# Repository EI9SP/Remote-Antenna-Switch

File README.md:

# Remote Antenna Switch
Four to one Remote Antenna Switch, Full duplex RS485.
Project contains:
4 to 1 remote switch with Atmel ATmega_328 chip on board.
Controller with ESP32 OLED display.
Communication betwen the modules is done over CAT5/CAT6 Cable utilising full duplex RS485 and 13.8V Power.

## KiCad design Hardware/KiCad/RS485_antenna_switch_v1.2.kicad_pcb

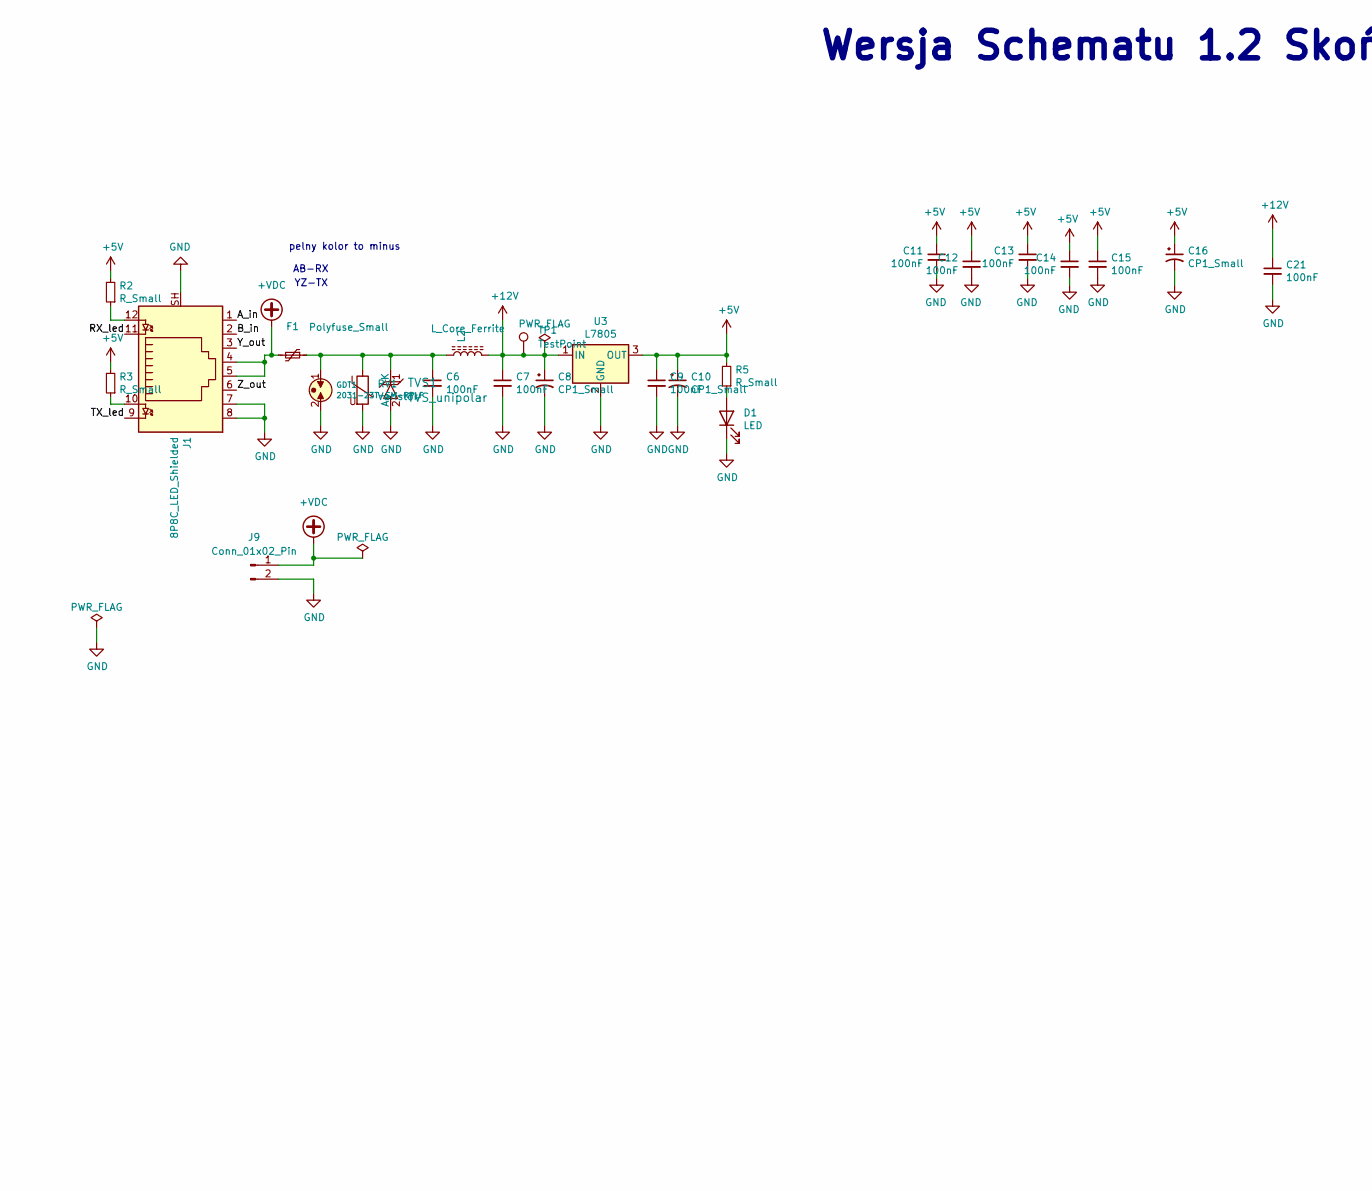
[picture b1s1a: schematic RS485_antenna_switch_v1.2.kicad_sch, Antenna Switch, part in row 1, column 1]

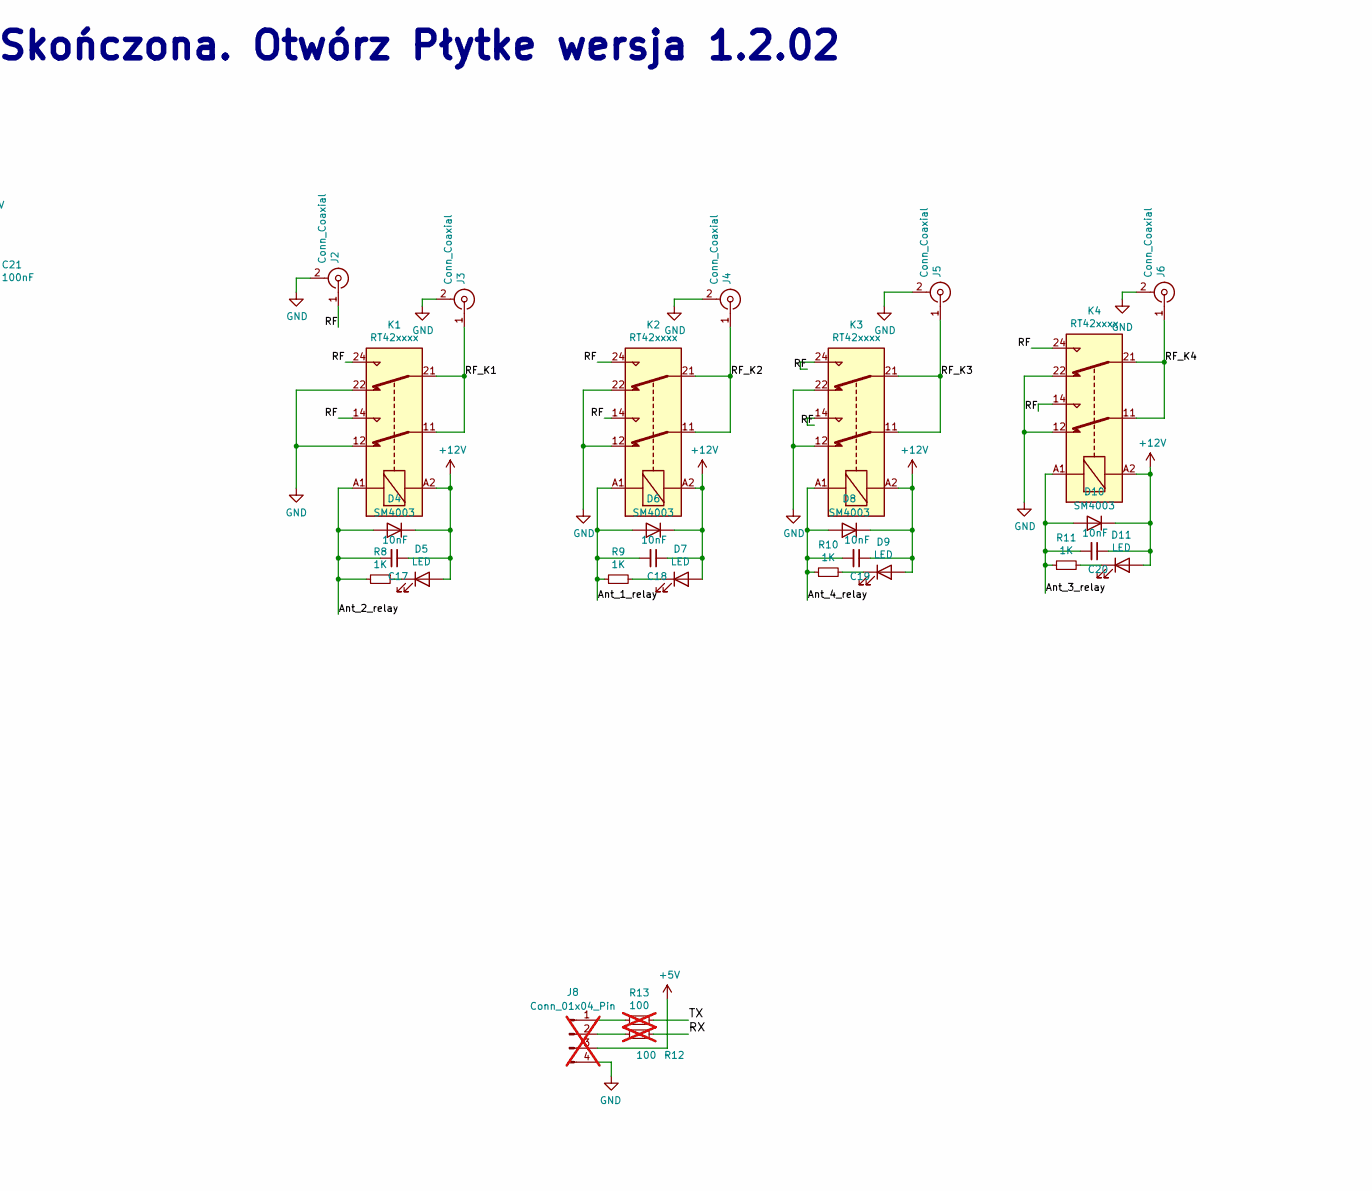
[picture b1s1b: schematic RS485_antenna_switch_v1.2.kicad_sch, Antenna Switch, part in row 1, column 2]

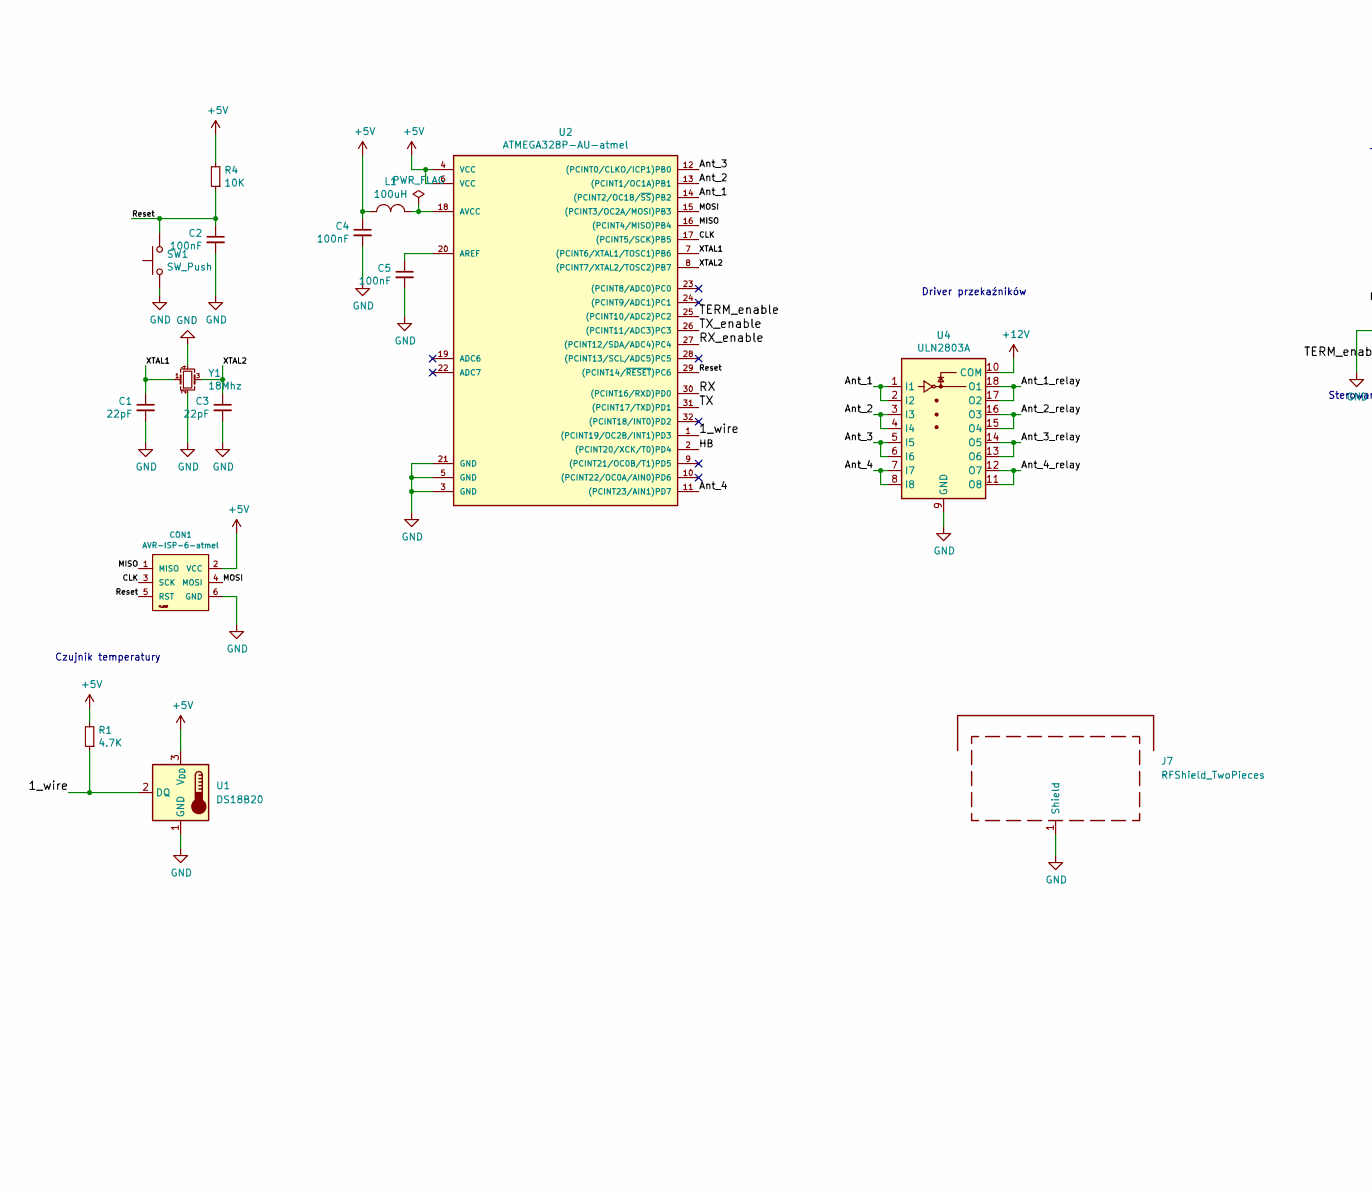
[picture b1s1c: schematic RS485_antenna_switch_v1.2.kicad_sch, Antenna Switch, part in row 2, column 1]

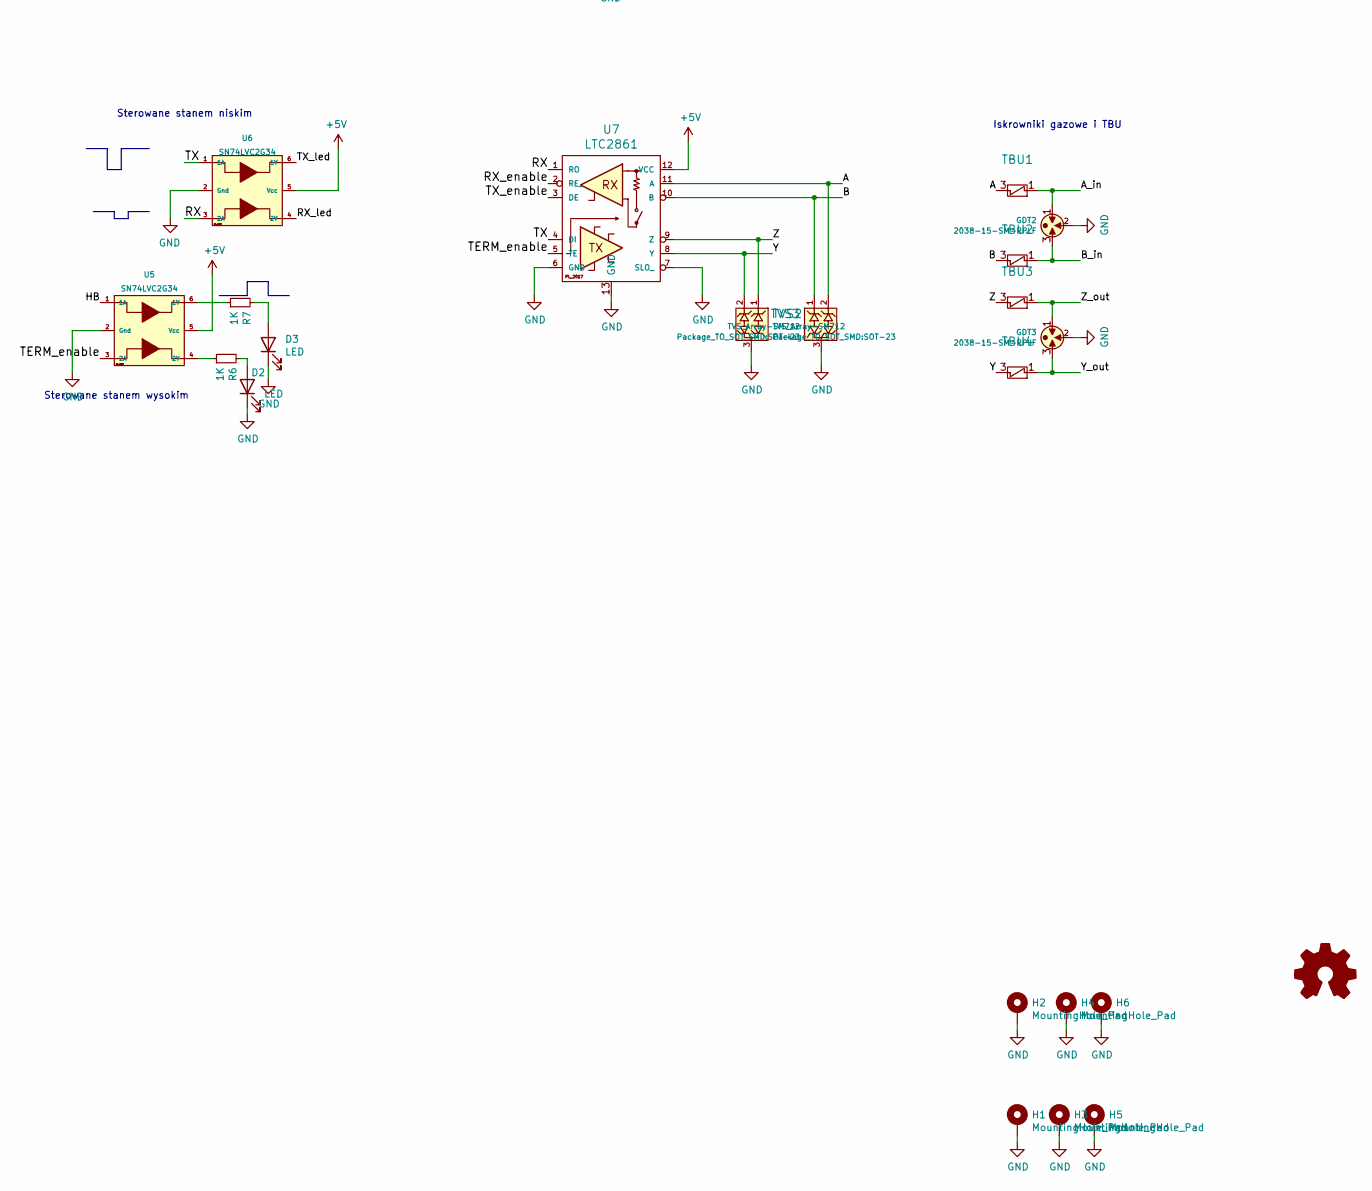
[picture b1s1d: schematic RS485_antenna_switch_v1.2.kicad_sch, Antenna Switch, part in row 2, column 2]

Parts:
C1: 22pF; C_0603_1608Metric
C2, C4, C5, C6, C7, C9, C11, C12, C13, C14, C15, C21: 100nF; C_0805_2012Metric
C3: 22pF; R_0603_1608Metric
C8, C10: CP1_Small; CP_EIA-7343-31_Kemet-D
C16: CP1_Small; CP_Elec_5x5.9
C17, C18, C19, C20: 10nF; C_0805_2012Metric
CON1: AVR-ISP-6-atmel; IDC-Header_2x03_P2.54mm_Vertical
D1, D2, D3: LED; LED_0805_2012Metric
D4, D6, D8, D10: SM4003; D_MELF
D5, D7, D9, D11: LED; LED_D3.0mm
F1: Polyfuse_Small; Fuse_Bourns_MF-SM_7.98x5.44mm
GDT1: 2031-23T-SM-RPLF; GDT-2027-XX-SM
GDT2, GDT3: 2038-15-SM-RPLF; GDT_2038-xx-SM
H1, H2, H3, H4, H5, H6: MountingHole_Pad; MountingHole_3.2mm_M3_Pad_Via
J1: 8P8C_LED_Shielded; RJ45_BEL_SS74301-00x_Vertical
J2, J3, J4, J5, J6: Conn_Coaxial; SO-239
J7: RFShield_TwoPieces
J8: Conn_01x04_Pin; Molex_KK-254_AE-6410-04A_1x04_P2.54mm_Vertical; not fitted
J9: Conn_01x02_Pin; PhoenixContact_MSTBVA_2,5_2-G-5,08_1x02_P5.08mm_Vertical
K1, K2, K3, K4: RT42xxxx; Relay_DPDT_Schrack-RT2-FormC_RM5mm
L1: 100uH; L_1812_4532Metric
L2: L_Core_Ferrite; Custom_inductors-BL01RN1A
R1: 4.7K; R_0805_2012Metric
R2, R3, R5: R_Small; R_0805_2012Metric
R4: 10K; R_0805_2012Metric
R6, R7, R8, R9, R10, R11: 1K; R_0805_2012Metric
R12, R13: 100; R_0805_2012Metric; not fitted
RV1: Varistor; RV_Disc_D12mm_W4.2mm_P7.5mm
SW1: SW_Push; SW_TH_Tactile_Omron_B3F-10xx
TBU1, TBU2, TBU3, TBU4: TBU_HSP; TBU-CA
TP1: TestPoint; TestPoint_THTPad_D2.0mm_Drill1.0mm
TVS1: TVS_unipolar; D_SMA
TVS2, TVS3: TVS_Array-SM712; SOT-23
U1: DS18B20; TO-92_HandSolder
U2: ATMEGA328P-AU-atmel; TQFP-32_7x7mm_P0.8mm
U3: L7805; d2-pak_termal
U4: ULN2803A; SOIC-18W_7.5x11.6mm_P1.27mm
U5, U6: SN74LVC2G34; SOT-23-6
U7: LTC2861; DFN-12-1EP_3x4mm_P0.5mm_EP1.7x3.3mm
Y1: 18Mhz; Crystal_SMD_5032-4Pin_5.0x3.2mm

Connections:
+5V: C4.1, C9.1, C10.1, C11.1, C12.1, C13.1, C14.1, C15.1, C16.1, CON1.2 (VCC), J8.3, L1.1, R1.2, R2.2, R3.2, R4.2, R5.2, U1.3 (V_{DD}), U2.4 (VCC), U2.6 (VCC), U3.3 (OUT), U5.5 (Vcc), U6.5 (Vcc), U7.12 (VCC)
+12V: C7.1, C8.1, C17.1, C18.1, C19.1, C20.1, C21.1, D4.1 (K), D5.2 (A), D6.1 (K), D7.2 (A), D8.1 (K), D9.2 (A), D10.1 (K), D11.2 (A), K1.A2, K2.A2, K3.A2, K4.A2, L2.2, TP1.1, U3.1 (IN), U4.10 (COM)
+VDC: F1.2, J1.4, J1.5, J9.1
/1_wire: R1.1, U1.2 (DQ), U2.1 ((PCINT19/OC2B/INT1)PD3)
/A: TBU1.3, TVS3.2, U7.11 (A)
/A_in: GDT2.1, J1.1, TBU1.1
/Ant_1: U2.14 ((PCINT2/OC1B/~SS)PB2), U4.1 (I1), U4.2 (I2)
/Ant_1_relay: C18.2, D6.2 (A), K2.A1, R9.1, U4.17 (O2), U4.18 (O1)
/Ant_2: U2.13 ((PCINT1/OC1A)PB1), U4.3 (I3), U4.4 (I4)
/Ant_2_relay: C17.2, D4.2 (A), K1.A1, R8.2, U4.15 (O4), U4.16 (O3)
/Ant_3: U2.12 ((PCINT0/CLKO/ICP1)PB0), U4.5 (I5), U4.6 (I6)
/Ant_3_relay: C20.2, D10.2 (A), K4.A1, R11.1, U4.13 (O6), U4.14 (O5)
/Ant_4: U2.11 ((PCINT23/AIN1)PD7), U4.7 (I7), U4.8 (I8)
/Ant_4_relay: C19.2, D8.2 (A), K3.A1, R10.1, U4.11 (O8), U4.12 (O7)
/B: TBU2.3, TVS3.1, U7.10 (B)
/B_in: GDT2.3, J1.2, TBU2.1
/CLK: CON1.3 (SCK), U2.17 ((PCINT5/SCK)PB5)
/HB: U2.2 ((PCINT20/XCK/T0)PD4), U5.1 (1A)
/MISO: CON1.1 (MISO), U2.16 ((PCINT4/MISO)PB4)
/MOSI: CON1.4 (MOSI), U2.15 ((PCINT3/OC2A/MOSI)PB3)
/RF: J2.1 (In), K1.14, K1.24, K2.14, K2.24, K3.14, K3.24, K4.14, K4.24
/RF_K1: J3.1 (In), K1.11, K1.21
/RF_K2: J4.1 (In), K2.11, K2.21
/RF_K3: J5.1 (In), K3.11, K3.21
/RF_K4: J6.1 (In), K4.11, K4.21
/RX: R12.1, U2.30 ((PCINT16/RXD)PD0), U6.3 (2A), U7.1 (RO)
/RX_enable: U2.27 ((PCINT12/SDA/ADC4)PC4), U7.2 (RE_)
/RX_led: J1.11, U6.4 (2Y)
/Reset: C2.1, CON1.5 (RST), R4.1, SW1.2, U2.29 ((PCINT14/~RESET)PC6)
/TERM_enable: U2.25 ((PCINT10/ADC2)PC2), U5.3 (2A), U7.5 (TE)
/TX: R13.1, U2.31 ((PCINT17/TXD)PD1), U6.1 (1A), U7.4 (DI)
/TX_enable: U2.26 ((PCINT11/ADC3)PC3), U7.3 (DE)
/TX_led: J1.9, U6.6 (1Y)
/XTAL1: C1.1, U2.7 ((PCINT6/XTAL1/TOSC1)PB6), Y1.1
/XTAL2: C3.1, U2.8 ((PCINT7/XTAL2/TOSC2)PB7), Y1.3
/Y: TBU4.3, TVS2.2, U7.8 (Y)
/Y_out: GDT3.3, J1.3, TBU4.1
/Z: TBU3.3, TVS2.1, U7.9 (Z)
/Z_out: GDT3.1, J1.6, TBU3.1
GND: C1.2, C2.2, C3.2, C4.2, C5.2, C6.2, C7.2, C8.2, C9.2, C10.2, C11.2, C12.2, C13.2, C14.2, C15.2, C16.2, C21.2, CON1.6 (GND), D1.1 (K), D2.1 (K), D3.1 (K), GDT1.2, GDT2.2, GDT3.2, H1.1, H2.1, H3.1, H4.1, H5.1, H6.1, J1.7, J1.8, J1.SH, J2.2 (Ext), J3.2 (Ext), J4.2 (Ext), J5.2 (Ext), J6.2 (Ext), J7.1, J8.4, J9.2, K1.12, K1.22, K2.12, K2.22, K3.12, K3.22, K4.12, K4.22, RV1.2, SW1.1, TVS1.2 (A), TVS2.3, TVS3.3, U1.1 (GND), U2.3 (GND), U2.5 (GND), U2.21 (GND), U3.2 (GND), U4.9 (GND), U5.2 (Gnd), U6.2 (Gnd), U7.6 (GND), U7.7 (SLO_), U7.13 (GND), Y1.2, Y1.4
unnamed: D1.2 (A), R5.1
unnamed: D2.2 (A), R6.2
unnamed: D3.2 (A), R7.2
unnamed: D5.1 (K), R8.1
unnamed: D7.1 (K), R9.2
unnamed: D9.1 (K), R10.2
unnamed: D11.1 (K), R11.2
unnamed: J1.10, R3.1
unnamed: J1.12, R2.1
unnamed: J8.1, R13.2
unnamed: J8.2, R12.2
unnamed: C6.1, F1.1, GDT1.1, L2.1, RV1.1, TVS1.1 (K)
unnamed: C5.1, U2.20 (AREF)
unnamed: L1.2, U2.18 (AVCC)
unnamed: R7.1, U5.6 (1Y)
unnamed: R6.1, U5.4 (2Y)

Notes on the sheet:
Wersja Schematu 1.2 Skończona. Otwórz Płytke wersja 1.2.02
AB-RX
Sterowane stanem niskim
Sterowane stanem wysokim
YZ-TX
pelny kolor to minus
Driver przekaźników
Iskrowniki gazowe i TBU
Czujnik temperatury

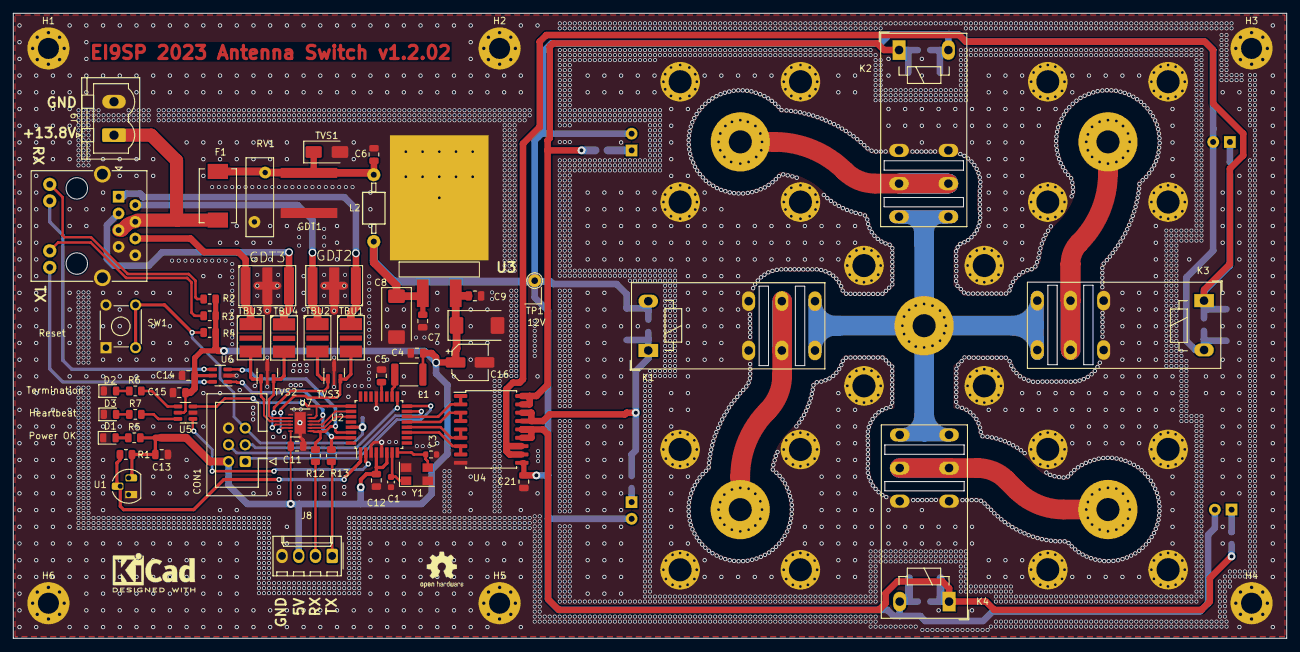
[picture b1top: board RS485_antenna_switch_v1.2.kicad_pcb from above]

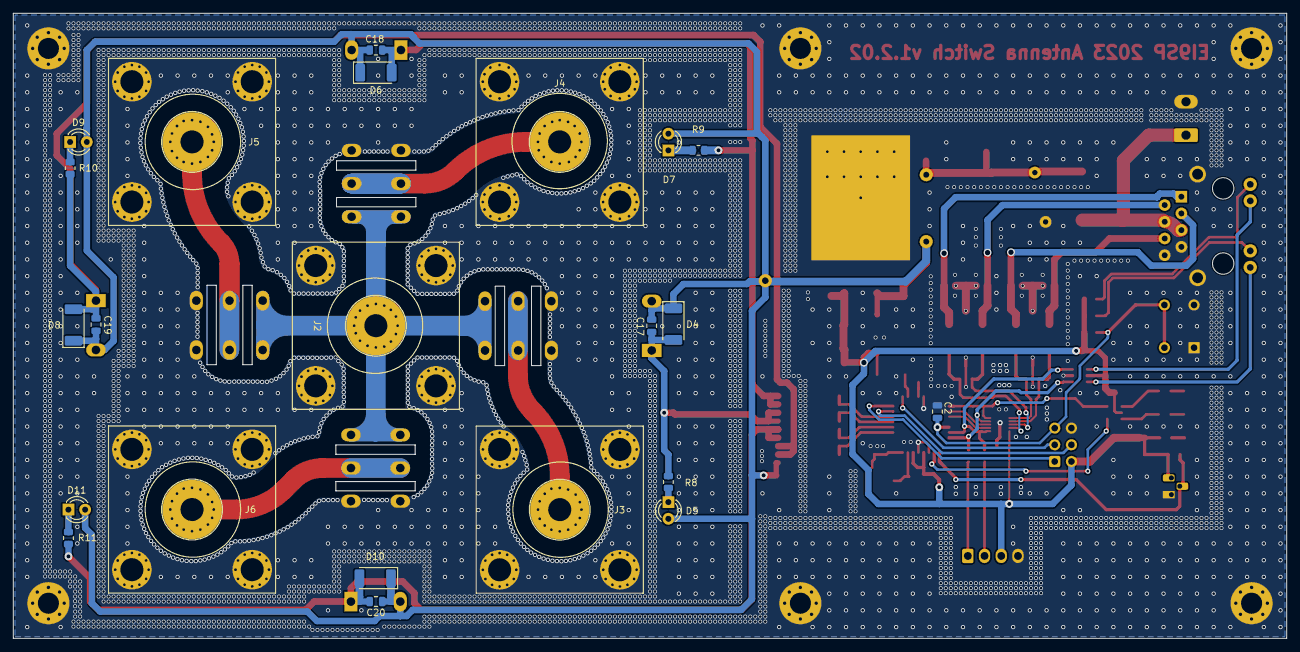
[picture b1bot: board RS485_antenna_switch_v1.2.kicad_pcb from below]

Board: 2 copper layers, 193.5 x 95.0 mm, 88 parts (22 on the bottom side), 56 nets.

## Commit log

2023-04-20 init
2023-04-23 Update to file structure. Implememnting new File System and mowing WEB to FS space. Implementing AP +STD WifiMode
2023-04-23 Adding Android App binaries and backup from MIT App Inventor
2023-04-23 Create Hardware
2023-09-02 Create Switch_board
    Kicad files 4:1 Antenna Switch
2023-09-02 Create Hardware
    Folder for Hardware files.
    Kicad components libraries.
    Kicad PCB design files.
2023-09-02 Create Hardware
    This folder contains hardware-related files.
    Kicad libraries used in the project
    Kicad PCB design files.
2023-09-02 Create Antenna_Switch
2023-09-02 Update Antenna_Switch
2023-10-09 Add files via upload
    New controller code for MaTouch ESP32-S3 by maker fab
2024-01-13 Winter cleaning
    Cleaning folder structure and reorganising files.
    Including current version of MA version
2024-01-13 typo
    typo
2024-01-13 formating
2024-01-13 Adding boards settings for compiler
2024-01-14 updating COM
    changing I2C to Serial
2024-01-24 Initial commit
    Display in simple version. Code needs cleanup and there might be still few bugs
2024-01-27 change too graphics
    replace drawing with png
2024-01-27 lvgl lib
2024-02-11 initial commit
    Migration from Arduino to PlatforIO. Code is not fully working but is compiling with no issues. Need to push to keep a save copy
